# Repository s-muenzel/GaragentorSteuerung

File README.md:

# GaragentorSteuerung

Remote-Steuerung für unser motorisiertes Garagentor.

## Hardware ##

### Garagenantrieb ###

Das Tor kann per 5V-Leitung getriggert werden.
Dabei lässt sich die Richtung (auf/zu) nicht auswählen (siehe Abschnitt Software)

Die Spannungsversorgung des eigentlichen Antriebs(Motor) läuft auf 24V, diese führe ich aus dem Gehäuse raus.
Falls Spannung anliegt hängt die Drehrichtung von der Polung ab (-+ / +-).

### Elektronisches und Micro-Controler ###

#### PCB ####

Mit 2 simplen Kontaktschaltern (Tastern) wird der Zustand "Tor (komplett) offen" bzw. "Tor (komplett) zu" gemeldet. 
Die Motorspannung (24V) geht per Vorwiderstand auf 2 Optokopler, die je nach Polung je einen Pin am Micro-Controler schalten.
Ein Optokopler schaltet dann den Antrieb.

#### Micro-Controler ####

Da gibt's natürlich viele Optionen, z.B. ein ESP-Board (8266 oder 32) mit genug GPIO Pins (mindestens *5*).

Ich nehme ein ESP8266 NodeMCU Board.

Für eine Schaltung mit einem Arduino (5V versus 3.3V) muss dann der Vorwiderstand vor OK1 angepasst werden.
Dann brauchts natürlich noch ein Wifi-Shield.

#### Pin-Belegung ####
PIN | GPIO | Belegung 
----
D8 | GPIO15 | Tor ist auf
D7 | GPIO13 | Tor ist zu
D6 | GPIO12 | Motor läuft hoch
D5 | GPIO14 | Motor läuft runter
D1 | GPIO5  | Antrieb-Trigger 

## Software ##

Benötigte Funktionalität:
- Wifi		(WLAN Zugriff generell)
- NTP		(Zeitsync)
- WebServer (Steuerung von aussen)
- *MQTT		(Alternative Steuerung)?*
- *OTA		(Für Updates ohne direkten Zugang)?*

Genereller Ablauf:
- Setup: Wifi, NTP, WebServer/MQTT aufsetzen, Ports konfigurieren
- Loop: Status Motor und Tor (Auf-Zu) monitoren, Falls zu den Tor-Zu-Zeiten das Tor länger nicht geschlossen ist, Tor schliessen

- WebServer:
	/: Tor auf,zu,öffnet gerade,schliesst gerade
	/Auf: Wenn möglich und nötig: Tor öffnen
	/Zu: Wenn möglich und nötig: Tor schliessen

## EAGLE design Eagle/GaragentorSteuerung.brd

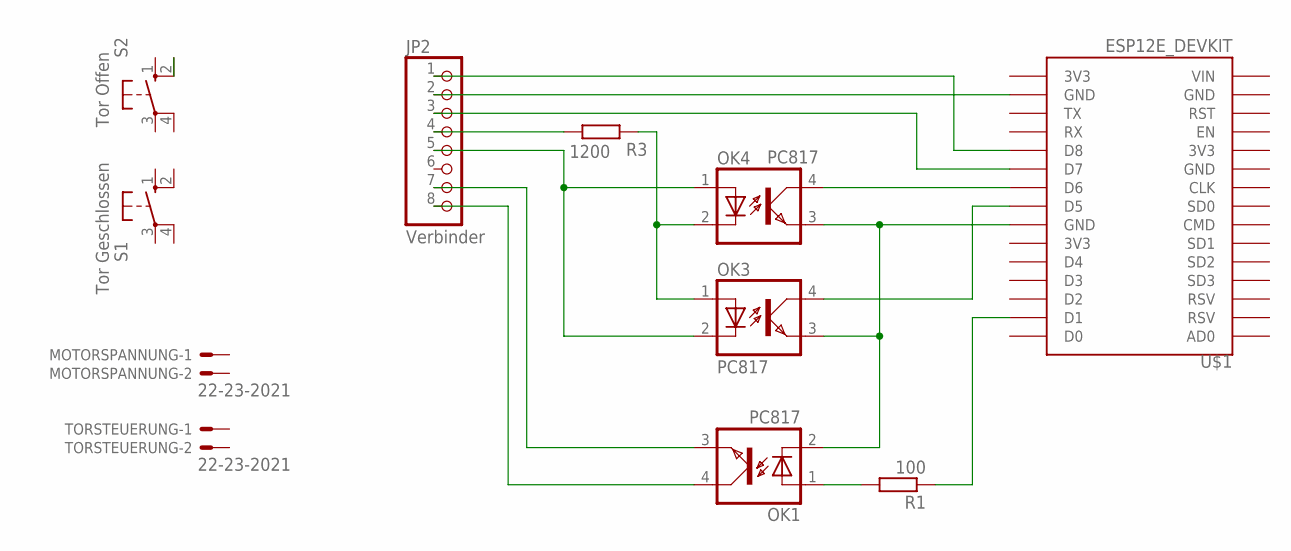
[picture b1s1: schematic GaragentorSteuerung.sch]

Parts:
JP2: Verbinder; 1X08
MOTORSPANNUNG: 22-23-2021
OK1, OK3, OK4: PC817; DIL04
R1: 100; 0207/7
R3: 1200; 0207/7
S1: Tor Geschlossen; B3F-10XX
S2: Tor Offen; B3F-10XX
TORSTEUERUNG: 22-23-2021
U$1: ESP12E_DEVKIT

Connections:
unnamed: JP2.1, U$1.D8
unnamed: JP2.2, U$1.GND@3 (GND)
unnamed: OK1.1 (A), R1.2
unnamed: OK4.4 (COL), U$1.D6
unnamed: JP2.5, OK3.2 (C), OK4.1 (A)
unnamed: OK3.1 (A), OK4.2 (C), R3.1
unnamed: OK1.2 (C), OK3.3 (EMIT), OK4.3 (EMIT), U$1.GND@2 (GND)
unnamed: OK3.4 (COL), U$1.D5
unnamed: R1.1, U$1.D1
unnamed: JP2.7, OK1.3 (EMIT)
unnamed: JP2.8, OK1.4 (COL)
unnamed: JP2.4, R3.2
unnamed: JP2.3, U$1.D7

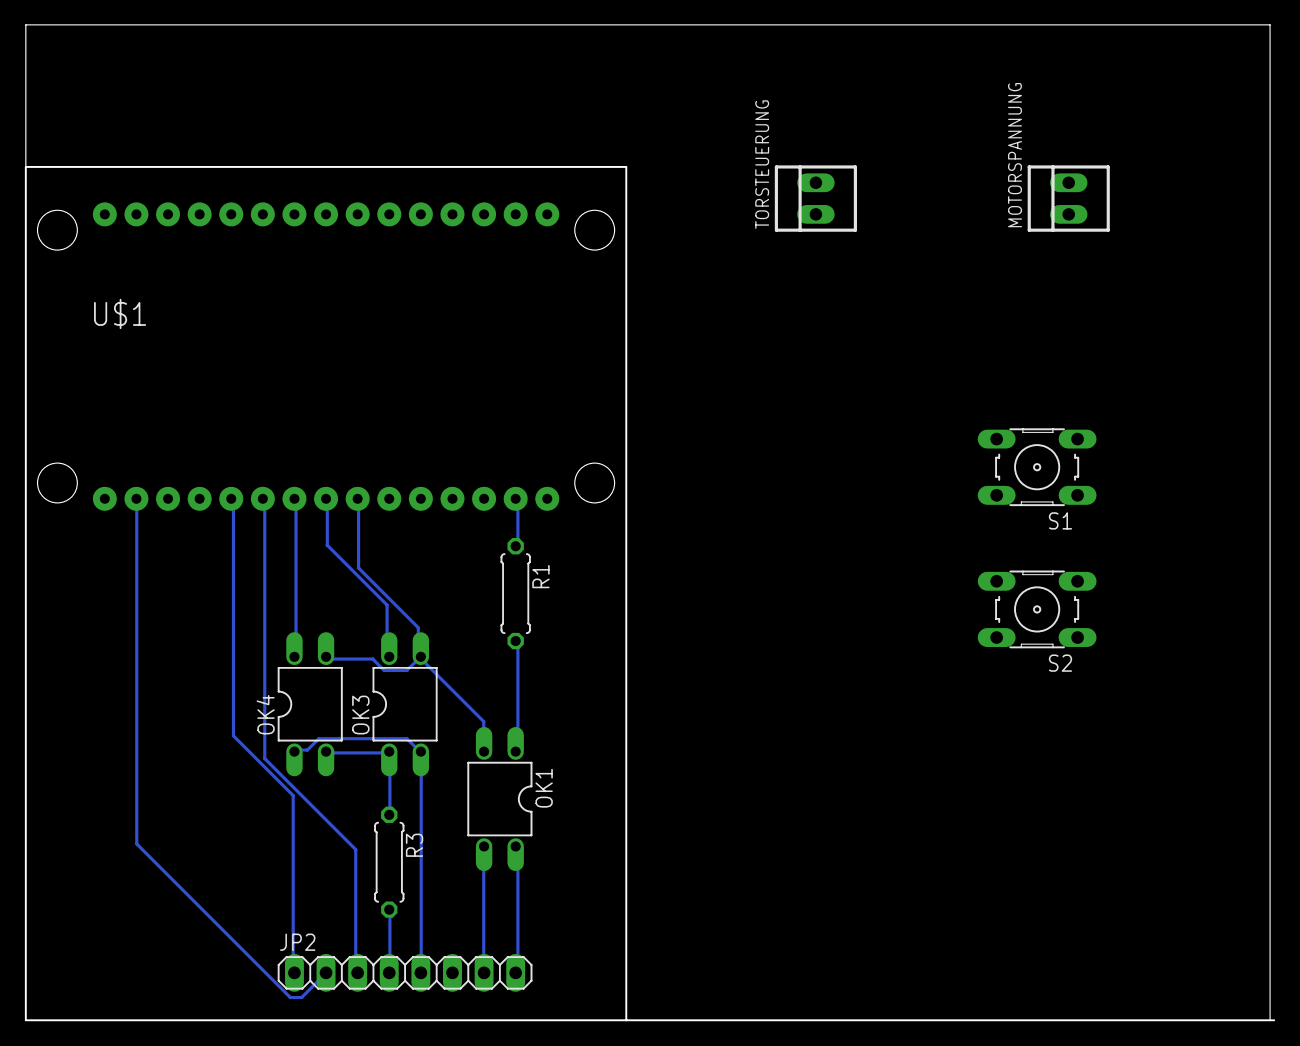
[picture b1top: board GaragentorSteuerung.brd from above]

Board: 2 copper layers, 100.3 x 80.0 mm, 11 parts (0 on the bottom side), 13 nets.

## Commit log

2019-01-15 Start
    erst Theorie & Docu
2019-01-15 Update Schema-PNG
    x
2019-01-15 Update Docu
    Immernoch nur Docu.
    SW kommt als nächstes
2019-01-16 SW V0
    Weitgehend leeres Skelett, Wifi, NTP und WebServer sind da und tun nix.
2019-01-16 V0.1
    sync
